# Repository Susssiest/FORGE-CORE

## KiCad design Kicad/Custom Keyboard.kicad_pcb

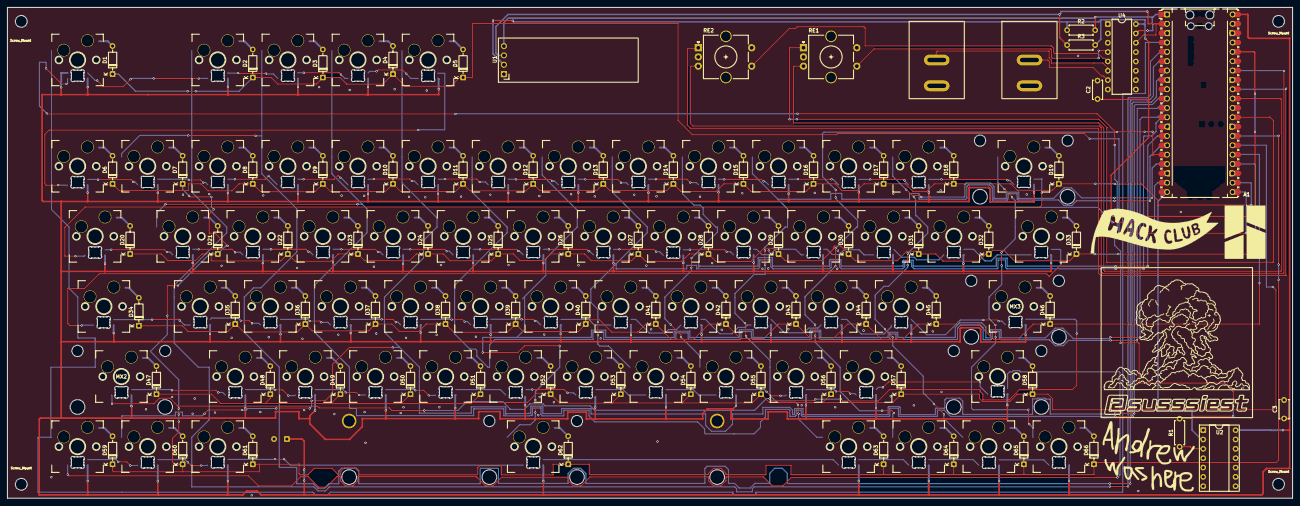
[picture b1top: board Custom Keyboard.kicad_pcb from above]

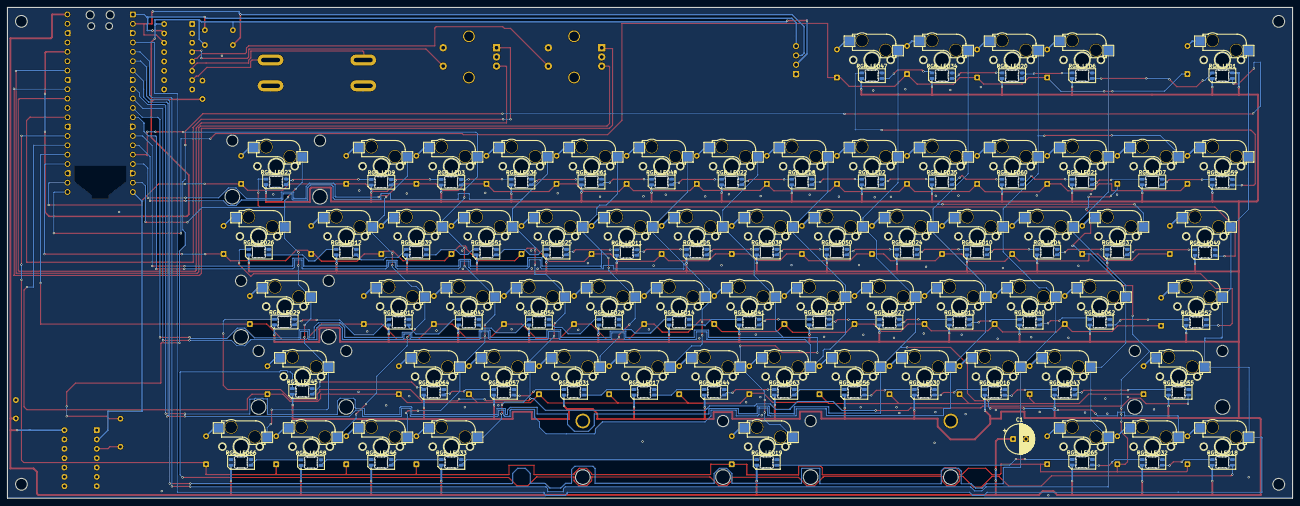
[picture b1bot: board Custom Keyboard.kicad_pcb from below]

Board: 2 copper layers, 349.3 x 133.3 mm, 222 parts (67 on the bottom side), 165 nets.

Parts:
A1: RaspberryPi_Pico; RaspberryPi_Pico_Common_Unspecified
C1: 1000uF; CP_Radial_D8.0mm_P3.50mm
C2, C3: 0.1uF; C_Disc_D5.0mm_W2.5mm_P5.00mm
D1, D2, D3, D4, D5, D6, D7, D8, D9, D10, D11, D12, D13, D14, D15, D16, D17, D18, D19, D20, D21, D22, D23, D24, D25, D26, D27, D28, D29, D30, D31, D32, D33, D34, D35, D36, D37, D38, D39, D40, D41, D42, D43, D44, D45, D46, D47, D48, D49, D50, D51, D52, D53, D54, D55, D56, D57, D58, D59, D60, D61, D62, D63, D64, D65, D66: 1N4148; D_DO-35_SOD27_P7.62mm_Horizontal
MX1: MX_stab; STAB_MX_P_6.25u
MX2, MX3: MX_stab; STAB_MX_2.25u
MX4: MX_stab; STAB_MX_2.75u
MX5, MX5#2: MX_stab; STAB_MX_2u
R1: 330; R_Axial_DIN0207_L6.3mm_D2.5mm_P7.62mm_Horizontal
R2, R3: 4.7k; R_Axial_DIN0207_L6.3mm_D2.5mm_P7.62mm_Horizontal
RE1, RE2: RotaryEncoder_Switch; RotaryEncoder_Alps_EC11E-Switch_Vertical_H20mm_CircularMoun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
RGB_LED1, RGB_LED2, RGB_LED3, RGB_LED4, RGB_LED5, RGB_LED6, RGB_LED7, RGB_LED8, RGB_LED9, RGB_LED10, RGB_LED11, RGB_LED12, RGB_LED13, RGB_LED14, RGB_LED15, RGB_LED16, RGB_LED17, RGB_LED18, RGB_LED19, RGB_LED20, RGB_LED21, RGB_LED22, RGB_LED23, RGB_LED24, RGB_LED25, RGB_LED26, RGB_LED27, RGB_LED28, RGB_LED29, RGB_LED30, RGB_LED31, RGB_LED32, RGB_LED33, RGB_LED34, RGB_LED35, RGB_LED36, RGB_LED37, RGB_LED38, RGB_LED39, RGB_LED40, RGB_LED41, RGB_LED42, RGB_LED43, RGB_LED44, RGB_LED45, RGB_LED46, RGB_LED47, RGB_LED48, RGB_LED49, RGB_LED50, RGB_LED51, RGB_LED52, RGB_LED53, RGB_LED54, RGB_LED55, RGB_LED56, RGB_LED57, RGB_LED58, RGB_LED59, RGB_LED60, RGB_LED61, RGB_LED62, RGB_LED63, RGB_LED64, RGB_LED65, RGB_LED66: LED; LED_SK6812MINI-E_3.2x2.8mm_P1.5mm_ReverseMount
SW1, SW2, SW3, SW4, SW5, SW6, SW7, SW8, SW9, SW10, SW11, SW12, SW13, SW14, SW15, SW16, SW17, SW18, SW19, SW20, SW21, SW22, SW23, SW24, SW25, SW26, SW27, SW28, SW29, SW30, SW31, SW32, SW33, SW34, SW35, SW36, SW37, SW38, SW39, SW40, SW41, SW42, SW43, SW44, SW45, SW46, SW47, SW48, SW49, SW50, SW51, SW52, SW53, SW54, SW55, SW56, SW57, SW58, SW59, SW60, SW61, SW62, SW63, SW64, SW65, SW66: SW_Push; MX_Hotswap
Screw_Mount: MountingHole_3.2mm_M3
Screw_Mount#2, Screw_Mount#3, Screw_Mount#4: MountingHole_3.2mm_M3
TS2, TS2#2: SW_SPST; KCD1_THT
U1: ER_OLEDM0.91_1x-I2C
U2: SN74AHCT125N; DIP-14_W7.62mm_Socket
U4: PCF8574AP; DIP-16_W7.62mm

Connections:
+3V3: A1.36 (3V3), C2.1, R2.1, R3.2, U1.2 (VCC), U4.16 (VDD)
+5V: A1.40 (VBUS), C1.1, C3.1, RGB_LED1.1 (VDD), RGB_LED1.3 (VSS), RGB_LED2.1 (VDD), RGB_LED3.1 (VDD), RGB_LED4.1 (VDD), RGB_LED5.1 (VDD), RGB_LED6.1 (VDD), RGB_LED7.1 (VDD), RGB_LED8.1 (VDD), RGB_LED9.1 (VDD), RGB_LED10.1 (VDD), RGB_LED11.1 (VDD), RGB_LED12.1 (VDD), RGB_LED13.1 (VDD), RGB_LED14.1 (VDD), RGB_LED15.1 (VDD), RGB_LED16.1 (VDD), RGB_LED17.1 (VDD), RGB_LED18.1 (VDD), RGB_LED19.1 (VDD), RGB_LED20.1 (VDD), RGB_LED21.1 (VDD), RGB_LED22.1 (VDD), RGB_LED23.1 (VDD), RGB_LED24.1 (VDD), RGB_LED25.1 (VDD), RGB_LED26.1 (VDD), RGB_LED27.1 (VDD), RGB_LED28.1 (VDD), RGB_LED29.1 (VDD), RGB_LED30.1 (VDD), RGB_LED31.1 (VDD), RGB_LED32.1 (VDD), RGB_LED33.1 (VDD), RGB_LED34.1 (VDD), RGB_LED35.1 (VDD), RGB_LED36.1 (VDD), RGB_LED37.1 (VDD), RGB_LED38.1 (VDD), RGB_LED39.1 (VDD), RGB_LED40.1 (VDD), RGB_LED41.1 (VDD), RGB_LED42.1 (VDD), RGB_LED43.1 (VDD), RGB_LED44.1 (VDD), RGB_LED45.1 (VDD), RGB_LED46.1 (VDD), RGB_LED47.1 (VDD), RGB_LED48.1 (VDD), RGB_LED49.1 (VDD), RGB_LED50.1 (VDD), RGB_LED51.1 (VDD), RGB_LED52.1 (VDD), RGB_LED53.1 (VDD), RGB_LED54.1 (VDD), RGB_LED55.1 (VDD), RGB_LED56.1 (VDD), RGB_LED57.1 (VDD), RGB_LED58.1 (VDD), RGB_LED59.1 (VDD), RGB_LED60.1 (VDD), RGB_LED61.1 (VDD), RGB_LED62.1 (VDD), RGB_LED63.1 (VDD), RGB_LED64.1 (VDD), RGB_LED65.1 (VDD), RGB_LED66.1 (VDD), U2.VCC
/C0: A1.4 (GPIO2), SW1.1, SW6.1, SW20.1, SW34.1, SW47.1, SW59.1
/C1: A1.5 (GPIO3), SW2.1, SW8.1, SW22.1, SW35.1, SW48.1, SW61.1
/C2: A1.6 (GPIO4), SW3.1, SW7.1, SW9.1, SW23.1, SW36.1, SW49.1
/C3: A1.7 (GPIO5), SW4.1, SW10.1, SW21.1, SW24.1, SW37.1, SW50.1
/C4: A1.9 (GPIO6), SW5.1, SW11.1, SW25.1, SW38.1, SW51.1, SW60.1
/C5: A1.10 (GPIO7), SW12.1, SW26.1, SW39.1, SW52.1
/C6: A1.11 (GPIO8), SW13.1, SW27.1, SW40.1, SW53.1, SW62.1
/C7: A1.12 (GPIO9), SW14.1, SW28.1, SW41.1, SW54.1
/C8: A1.14 (GPIO10), SW15.1, SW29.1, SW42.1, SW55.1
/C9: A1.15 (GPIO11), SW16.1, SW30.1, SW43.1, SW56.1, SW63.1
/C10: A1.16 (GPIO12), SW17.1, SW31.1, SW44.1, SW57.1, SW64.1
/C11: A1.17 (GPIO13), SW18.1, SW32.1, SW45.1, SW65.1
/C12: A1.19 (GPIO14), SW19.1, SW33.1, SW46.1, SW58.1, SW66.1
/Net-(RGB_LED1-DIN): R1.2, RGB_LED1.4 (DIN)
/R0: A1.21 (GPIO16), D1.1 (K), D2.1 (K), D3.1 (K), D4.1 (K), D5.1 (K)
/R1: A1.22 (GPIO17), D6.1 (K), D8.1 (K), D9.1 (K), D10.1 (K), D11.1 (K), D12.1 (K), D13.1 (K), D14.1 (K), D15.1 (K), D16.1 (K), D17.1 (K), D18.1 (K), D19.1 (K)
/R2: A1.24 (GPIO18), D20.1 (K), D22.1 (K), D23.1 (K), D24.1 (K), D25.1 (K), D26.1 (K), D27.1 (K), D28.1 (K), D29.1 (K), D30.1 (K), D31.1 (K), D32.1 (K), D33.1 (K)
/R3: A1.25 (GPIO19), D34.1 (K), D35.1 (K), D36.1 (K), D37.1 (K), D38.1 (K), D39.1 (K), D40.1 (K), D41.1 (K), D42.1 (K), D43.1 (K), D44.1 (K), D45.1 (K), D46.1 (K)
/R4: A1.26 (GPIO20), D47.1 (K), D48.1 (K), D49.1 (K), D50.1 (K), D51.1 (K), D52.1 (K), D53.1 (K), D54.1 (K), D55.1 (K), D56.1 (K), D57.1 (K), D58.1 (K)
/R5: A1.27 (GPIO21), D7.1 (K), D21.1 (K), D59.1 (K), D60.1 (K), D61.1 (K), D62.1 (K), D63.1 (K), D64.1 (K), D65.1 (K), D66.1 (K)
/RE1A: A1.29 (GPIO22), RE1.A
/RE1B: A1.31 (GPIO26_ADC0), RE1.B
/RE1BUTTON: RE1.S1, U4.4 (P0)
/RE2B: A1.34 (GPIO28_ADC2), RE2.B
/RE2_BUTTON: RE2.S1, U4.5 (P1)
/RGB Data: A1.20 (GPIO15), U2.1A
/SCL: A1.2 (GPIO1), R3.1, U1.3 (SCL), U4.14 (SCL)
/SDA: A1.1 (GPIO0), R2.2, U1.4 (SDA), U4.15 (SDA)
/SPST1: TS2.1 (A), U4.6 (P2)
/SPST2: TS2#2.1 (A), U4.7 (P3)
GND: A1.3 (GND), A1.8 (GND), A1.13 (GND), A1.18 (GND), A1.23 (GND), A1.28 (GND), A1.38 (GND), C1.2, C2.2, C3.2, RE1.C, RE1.S2, RE2.C, RGB_LED2.3 (VSS), RGB_LED3.3 (VSS), RGB_LED4.3 (VSS), RGB_LED5.3 (VSS), RGB_LED6.3 (VSS), RGB_LED7.3 (VSS), RGB_LED8.3 (VSS), RGB_LED9.3 (VSS), RGB_LED10.3 (VSS), RGB_LED11.3 (VSS), RGB_LED12.3 (VSS), RGB_LED13.3 (VSS), RGB_LED14.3 (VSS), RGB_LED15.3 (VSS), RGB_LED16.3 (VSS), RGB_LED17.3 (VSS), RGB_LED18.3 (VSS), RGB_LED19.3 (VSS), RGB_LED20.3 (VSS), RGB_LED21.3 (VSS), RGB_LED22.3 (VSS), RGB_LED23.3 (VSS), RGB_LED24.3 (VSS), RGB_LED25.3 (VSS), RGB_LED26.3 (VSS), RGB_LED27.3 (VSS), RGB_LED28.3 (VSS), RGB_LED29.3 (VSS), RGB_LED30.3 (VSS), RGB_LED31.3 (VSS), RGB_LED32.3 (VSS), RGB_LED33.3 (VSS), RGB_LED34.3 (VSS), RGB_LED35.3 (VSS), RGB_LED36.3 (VSS), RGB_LED37.3 (VSS), RGB_LED38.3 (VSS), RGB_LED39.3 (VSS), RGB_LED40.3 (VSS), RGB_LED41.3 (VSS), RGB_LED42.3 (VSS), RGB_LED43.3 (VSS), RGB_LED44.3 (VSS), RGB_LED45.3 (VSS), RGB_LED46.3 (VSS), RGB_LED47.3 (VSS), RGB_LED48.3 (VSS), RGB_LED49.3 (VSS), RGB_LED50.3 (VSS), RGB_LED51.3 (VSS), RGB_LED52.3 (VSS), RGB_LED53.3 (VSS), RGB_LED54.3 (VSS), RGB_LED55.3 (VSS), RGB_LED56.3 (VSS), RGB_LED57.3 (VSS), RGB_LED58.3 (VSS), RGB_LED59.3 (VSS), RGB_LED60.3 (VSS), RGB_LED61.3 (VSS), RGB_LED62.3 (VSS), RGB_LED63.3 (VSS), RGB_LED64.3 (VSS), RGB_LED65.3 (VSS), RGB_LED66.3 (VSS), TS2.1 (A), TS2#2.1 (A), U1.1 (GND), U2.1OE, U2.2A, U2.2OE, U2.3A, U2.3OE, U2.4A, U2.4OE, U2.GND, U4.1 (A0), U4.2 (A1), U4.3 (A2), U4.8 (GND)
unnamed: D1.2 (A), SW1.2
unnamed: D2.2 (A), SW2.2
unnamed: D3.2 (A), SW3.2
unnamed: D4.2 (A), SW4.2
unnamed: D5.2 (A), SW5.2
unnamed: D6.2 (A), SW6.2
unnamed: D7.2 (A), SW7.2
unnamed: D8.2 (A), SW8.2
unnamed: D9.2 (A), SW9.2
unnamed: D10.2 (A), SW10.2
unnamed: D11.2 (A), SW11.2
unnamed: D12.2 (A), SW12.2
unnamed: D13.2 (A), SW13.2
unnamed: D14.2 (A), SW14.2
unnamed: D15.2 (A), SW15.2
unnamed: D16.2 (A), SW16.2
unnamed: D17.2 (A), SW17.2
unnamed: D18.2 (A), SW18.2
unnamed: D19.2 (A), SW19.2
unnamed: D20.2 (A), SW20.2
unnamed: D21.2 (A), SW21.2
unnamed: D22.2 (A), SW22.2
unnamed: D23.2 (A), SW23.2
unnamed: D24.2 (A), SW24.2
unnamed: D25.2 (A), SW25.2
unnamed: D26.2 (A), SW26.2
unnamed: D27.2 (A), SW27.2
unnamed: D28.2 (A), SW28.2
unnamed: D29.2 (A), SW29.2
unnamed: D30.2 (A), SW30.2
unnamed: D31.2 (A), SW31.2
unnamed: D32.2 (A), SW32.2
unnamed: D33.2 (A), SW33.2
unnamed: D34.2 (A), SW34.2
unnamed: D35.2 (A), SW35.2
unnamed: D36.2 (A), SW36.2
unnamed: D37.2 (A), SW37.2
unnamed: D38.2 (A), SW38.2
unnamed: D39.2 (A), SW39.2
unnamed: D40.2 (A), SW40.2
unnamed: D41.2 (A), SW41.2
unnamed: D42.2 (A), SW42.2
unnamed: D43.2 (A), SW43.2
unnamed: D44.2 (A), SW44.2
unnamed: D45.2 (A), SW45.2
unnamed: D46.2 (A), SW46.2
unnamed: D47.2 (A), SW47.2
unnamed: D48.2 (A), SW48.2
unnamed: D49.2 (A), SW49.2
unnamed: D50.2 (A), SW50.2
unnamed: D51.2 (A), SW51.2
unnamed: D52.2 (A), SW52.2
unnamed: D53.2 (A), SW53.2
unnamed: D54.2 (A), SW54.2
unnamed: D55.2 (A), SW55.2
unnamed: D56.2 (A), SW56.2
unnamed: D57.2 (A), SW57.2
unnamed: D58.2 (A), SW58.2
unnamed: D59.2 (A), SW59.2
unnamed: D60.2 (A), SW60.2
unnamed: D61.2 (A), SW61.2
unnamed: D62.2 (A), SW62.2
unnamed: D63.2 (A), SW63.2
unnamed: D64.2 (A), SW64.2
unnamed: D65.2 (A), SW65.2
unnamed: D66.2 (A), SW66.2
unnamed: RGB_LED1.2 (DOUT), RGB_LED6.4 (DIN)
unnamed: RGB_LED2.4 (DIN), RGB_LED35.2 (DOUT)
unnamed: RGB_LED2.2 (DOUT), RGB_LED8.4 (DIN)
unnamed: RGB_LED3.4 (DIN), RGB_LED36.2 (DOUT)
unnamed: RGB_LED3.2 (DOUT), RGB_LED9.4 (DIN)
unnamed: RGB_LED4.2 (DOUT), RGB_LED10.4 (DIN)
unnamed: RGB_LED10.2 (DOUT), RGB_LED24.4 (DIN)
unnamed: RGB_LED5.2 (DOUT), RGB_LED11.4 (DIN)
unnamed: RGB_LED11.2 (DOUT), RGB_LED25.4 (DIN)
unnamed: RGB_LED12.4 (DIN), RGB_LED39.2 (DOUT)
unnamed: RGB_LED12.2 (DOUT), RGB_LED26.4 (DIN)
unnamed: RGB_LED13.4 (DIN), RGB_LED40.2 (DOUT)
unnamed: RGB_LED13.2 (DOUT), RGB_LED27.4 (DIN)
unnamed: RGB_LED14.4 (DIN), RGB_LED41.2 (DOUT)
unnamed: RGB_LED14.2 (DOUT), RGB_LED28.4 (DIN)
unnamed: RGB_LED15.4 (DIN), RGB_LED42.2 (DOUT)
unnamed: RGB_LED15.2 (DOUT), RGB_LED29.4 (DIN)
unnamed: RGB_LED16.4 (DIN), RGB_LED43.2 (DOUT)
unnamed: RGB_LED16.2 (DOUT), RGB_LED30.4 (DIN)
unnamed: RGB_LED17.4 (DIN), RGB_LED44.2 (DOUT)
unnamed: RGB_LED17.2 (DOUT), RGB_LED31.4 (DIN)
unnamed: RGB_LED18.4 (DIN), RGB_LED45.2 (DOUT)
unnamed: RGB_LED18.2 (DOUT), RGB_LED32.4 (DIN)
unnamed: RGB_LED19.4 (DIN), RGB_LED65.2 (DOUT)
unnamed: RGB_LED19.2 (DOUT), RGB_LED33.4 (DIN)
unnamed: RGB_LED6.2 (DOUT), RGB_LED20.4 (DIN)
unnamed: RGB_LED20.2 (DOUT), RGB_LED34.4 (DIN)
unnamed: RGB_LED7.2 (DOUT), RGB_LED21.4 (DIN)
unnamed: RGB_LED21.2 (DOUT), RGB_LED60.4 (DIN)
unnamed: RGB_LED8.2 (DOUT), RGB_LED22.4 (DIN)
unnamed: RGB_LED22.2 (DOUT), RGB_LED48.4 (DIN)
unnamed: RGB_LED9.2 (DOUT), RGB_LED23.4 (DIN)
unnamed: RGB_LED23.2 (DOUT), RGB_LED49.4 (DIN)
unnamed: RGB_LED24.2 (DOUT), RGB_LED50.4 (DIN)
unnamed: RGB_LED25.2 (DOUT), RGB_LED51.4 (DIN)
unnamed: RGB_LED26.2 (DOUT), RGB_LED52.4 (DIN)
unnamed: RGB_LED27.2 (DOUT), RGB_LED53.4 (DIN)
unnamed: RGB_LED28.2 (DOUT), RGB_LED54.4 (DIN)
unnamed: RGB_LED29.2 (DOUT), RGB_LED55.4 (DIN)
unnamed: RGB_LED30.2 (DOUT), RGB_LED56.4 (DIN)
unnamed: RGB_LED31.2 (DOUT), RGB_LED57.4 (DIN)
unnamed: RGB_LED32.2 (DOUT), RGB_LED65.4 (DIN)
unnamed: RGB_LED33.2 (DOUT), RGB_LED46.4 (DIN)
unnamed: RGB_LED34.2 (DOUT), RGB_LED47.4 (DIN)
unnamed: RGB_LED35.4 (DIN), RGB_LED60.2 (DOUT)
unnamed: RGB_LED36.4 (DIN), RGB_LED61.2 (DOUT)
unnamed: RGB_LED37.4 (DIN), RGB_LED49.2 (DOUT)
unnamed: RGB_LED4.4 (DIN), RGB_LED37.2 (DOUT)
unnamed: RGB_LED38.4 (DIN), RGB_LED50.2 (DOUT)
unnamed: RGB_LED5.4 (DIN), RGB_LED38.2 (DOUT)
unnamed: RGB_LED39.4 (DIN), RGB_LED51.2 (DOUT)
unnamed: RGB_LED40.4 (DIN), RGB_LED62.2 (DOUT)
unnamed: RGB_LED41.4 (DIN), RGB_LED53.2 (DOUT)
unnamed: RGB_LED42.4 (DIN), RGB_LED54.2 (DOUT)
unnamed: RGB_LED43.4 (DIN), RGB_LED55.2 (DOUT)
unnamed: RGB_LED44.4 (DIN), RGB_LED63.2 (DOUT)
unnamed: RGB_LED45.4 (DIN), RGB_LED64.2 (DOUT)
unnamed: RGB_LED46.2 (DOUT), RGB_LED58.4 (DIN)
unnamed: RGB_LED47.2 (DOUT), RGB_LED59.4 (DIN)
unnamed: RGB_LED48.2 (DOUT), RGB_LED61.4 (DIN)
unnamed: RGB_LED52.2 (DOUT), RGB_LED62.4 (DIN)
unnamed: RGB_LED56.2 (DOUT), RGB_LED63.4 (DIN)
unnamed: RGB_LED57.2 (DOUT), RGB_LED64.4 (DIN)
unnamed: RGB_LED58.2 (DOUT), RGB_LED66.4 (DIN)
unnamed: RGB_LED7.4 (DIN), RGB_LED59.2 (DOUT)
RGB_Out: R1.1, U2.1Y
